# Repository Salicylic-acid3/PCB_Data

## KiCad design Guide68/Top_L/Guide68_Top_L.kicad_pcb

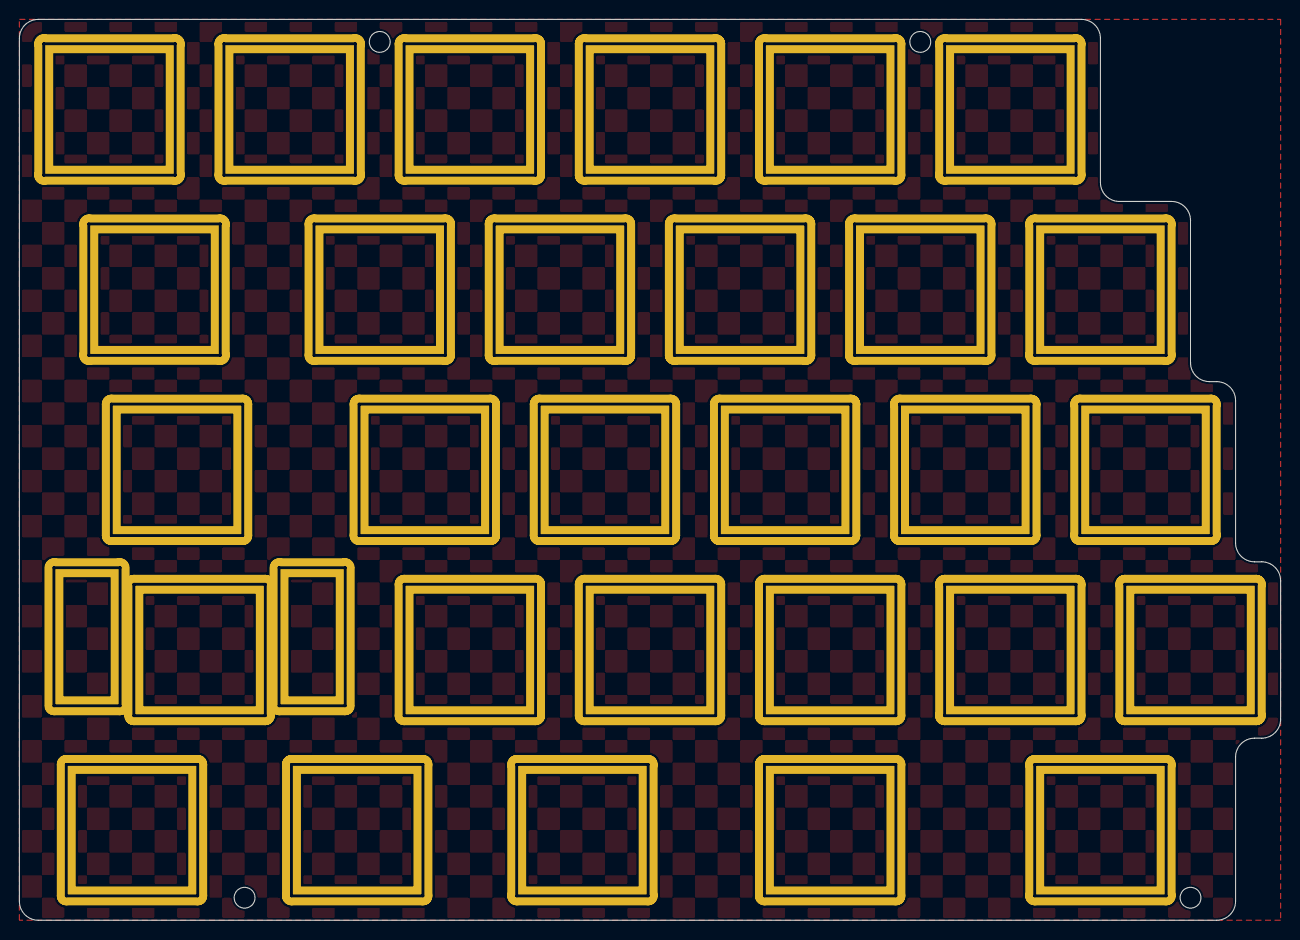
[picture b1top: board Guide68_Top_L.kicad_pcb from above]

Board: 2 copper layers, 133.3 x 95.2 mm, 33 parts (0 on the bottom side), 6 nets, no tracks yet.

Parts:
Ref**: Val**; m2_Screw_Hole
Ref**#2, Ref**#3, Ref**#4: Val**; m2_Screw_Hole
SW1, SW2, SW3, SW5, SW6, SW7, SW8, SW9, SW10, SW11, SW12, SW13, SW14, SW15, SW16, SW17, SW18, SW19, SW20, SW21, SW22, SW23, SW24, SW25, SW26, SW27, SW28, SW29: SW_PUSH; SW_Hole_TH_1u
SW4: SW_PUSH; SW_Hole_TH_2u

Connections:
Col0: SW1.1, SW2.1, SW3.1, SW4.1, SW5.1
Col1: SW6.1, SW7.1, SW8.1, SW9.1, SW10.1
Col2: SW11.1, SW12.1, SW13.1, SW14.1, SW15.1
Col3: SW16.1, SW17.1, SW18.1, SW19.1, SW20.1
Col4: SW21.1, SW22.1, SW23.1, SW24.1, SW25.1
Col5: SW26.1, SW27.1, SW28.1, SW29.1
